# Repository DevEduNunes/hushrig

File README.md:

<div align="center">

# 🎸 HushRig

**Rig de guitarra open source para Windows — standalone e VST3.**
Toque direto no PC com baixa latência e sem chiado.

</div>

---

## Por que o HushRig?

Guitarra ligada direto no PC costuma dar dois problemas: **chiado** (captadores single coil, ganho alto, ruído da USB) e **delay** (drivers de áudio padrão do Windows com buffers grandes).
O HushRig ataca os dois: um **noise gate de latência zero** feito para guitarra e um caminho de áudio pensado para rodar com **ASIO**.

> ⚠️ Projeto em desenvolvimento ativo (v0.2). Gate, pedais, presets e amp sim NAM já funcionam; a interface com pedais visuais está no [roadmap](#-roadmap).

## ✨ Recursos

- **Medidor de latência**: mostra em ms a latência real reportada pelo driver (entrada, saída, buffer, CPU) com dicas para reduzir
- **Medidores de nível** de entrada e saída, com marcador do threshold e indicador de gate aberto/fechado
- **Pedais** de overdrive, EQ, chorus, delay e reverb, com ordem ajustável (arraste) e **presets** (de fábrica e seus)
- **Amp sim** com modelos `.nam` do [Neural Amp Modeler](https://www.neuralampmodeler.com/): 0 ms de latência adicionada, controles de ganho, graves/médios/agudos e volume, normalização de volume entre modelos e medidor de CPU
- **Noise gate** com threshold, hold e release — sem lookahead, ou seja, **zero latência** adicionada
- **Gravação em WAV** (24 bits, áudio já processado) com um clique, salva em Documentos\HushRig
- **Tema escuro** (preto e roxo) com knobs rotativos
- **Ganho de entrada e de saída** com transição suave (sem cliques)
- **Standalone e VST3** com o mesmo código
- **Entrada mono** espelhada nos dois canais (guitarra em estéreo no fone)
- **Janela redimensionável e botão de maximizar**: os cards se reorganizam em 1, 2 ou 3 colunas conforme o tamanho (monitor horizontal ou vertical) e podem ser arrastados para outra posição; a ordem fica salva
- **Atualização dentro do app**: ao abrir, procura novas versões no GitHub; se houver, aparece um ícone de download na barra de título e um clique baixa e instala
- **Instalador completo** que já instala o driver ASIO [FlexASIO](https://github.com/dechamps/FlexASIO)

## 🖼️ Screenshots

<table>
  <tr>
    <td align="center"><br><sub>Tela principal</sub></td>
  </tr>
</table>

> As imagens são geradas automaticamente pelo CI a cada build (`tools/Screenshots.cpp`). Os valores de latência e de nível nelas são **de exemplo**.

## 📦 Instalação

1. Baixe o `HushRig-Setup-x.y.z.exe` na página de [Releases](https://github.com/DevEduNunes/hushrig/releases).
2. Execute o instalador. Você escolhe os componentes:
   - **HushRig** (aplicativo)
   - **Plugin VST3** (instalado em `Common Files\VST3`)
   - **FlexASIO** (driver ASIO de baixa latência)
3. Abra o HushRig.

> O Windows pode mostrar o aviso do SmartScreen ("editor desconhecido"), porque o instalador ainda não é assinado digitalmente. Clique em **Mais informações → Executar assim mesmo**.

## 🎚️ Como usar

1. Conecte a interface de áudio e a guitarra. **Use fones** para evitar microfonia.
2. Em **Options** (canto do app), escolha o driver **ASIO → FlexASIO**, a entrada e a saída. Desmarque *Mute audio input*.
3. Reduza o **buffer** (comece com 256 amostras e vá descendo até começar a estalar) para diminuir a latência.
4. Ajuste o **Gate Threshold** até o chiado sumir quando você não está tocando. Se o gate cortar o fim das notas, aumente o **Release**.

| Parâmetro | O que faz |
|---|---|
| **Input Gain** | Ganho aplicado antes do gate |
| **Gate Threshold** | Nível abaixo do qual o gate fecha |
| **Gate Hold** | Tempo que o gate segura aberto depois que o sinal cai |
| **Gate Release** | Quão rápido o gate fecha |
| **Output Gain** | Volume de saída |
| **Gate bypass** | Desliga o gate |

### Pedais e presets

Ligue cada pedal no botão do canto do bloco. **Arraste o título** de um bloco para mudar a ordem da cadeia. O seletor **Presets** traz alguns de fábrica e guarda os seus (**Salvar**/**Excluir**), em `Documentos\HushRig\Presets`. Um preset guarda os pedais, a ordem e o modelo do amp; ganhos e gate ficam como você deixou.

### Amp sim (modelos NAM)

1. No bloco **AMP (NAM)**, clique em **Carregar modelo...** e escolha um arquivo `.nam` (ou um `.wav` de IR). Há muitos modelos gratuitos feitos pela comunidade do [Neural Amp Modeler](https://www.neuralampmodeler.com/).
2. O bloco mostra quanto do tempo do buffer o modelo usa (**CPU**). Se ficar alto (laranja/vermelho) ou o som estalar, troque por um modelo mais leve ou aumente o buffer.
3. No card **AMP · GANHO E TOM** ajuste:

| Controle | O que faz |
|---|---|
| **Input** | Ganho antes do modelo (empurra o amp para mais ou menos distorção) |
| **Bass / Mid / Treble** | Tom, aplicado depois do modelo (±12 dB) |
| **Output** | Volume de saída do amp |
| **Normalizar volume** | Iguala o volume entre modelos usando o loudness gravado no `.nam` |

O amp **não adiciona latência**. Se o modelo foi treinado em uma taxa diferente da do dispositivo (por exemplo 48 kHz no modelo e 44,1 kHz no driver), o bloco avisa, porque o timbre muda: prefira rodar a 48 kHz.

### Dicas contra o chiado

O software ajuda, mas confira também a origem:
- Ganho do preamp da interface alto demais
- Captadores single coil (chegar perto do monitor aumenta o zumbido)
- Notebook ligado na fonte (teste na bateria) e outra porta USB
- Cabo da guitarra

## 🔄 Atualizações

No app standalone, toda vez que você abre o HushRig ele procura uma versão nova no GitHub. Se houver, aparece um ícone de download com o número da versão na barra de título: clique nele e o app baixa o instalador da release, confere o SHA-256 e reinicia já atualizado.

## 🗺️ Roadmap

- [x] Esqueleto JUCE (Standalone + VST3) e CI no GitHub Actions
- [x] Noise gate (threshold, hold, release) com testes
- [x] Instalador com FlexASIO e atualização dentro do app
- [x] Medidor de latência e medidores de nível
- [x] Pedais: overdrive, delay, reverb, chorus e EQ
- [x] Cadeia de pedais reordenável (arraste o título) e presets
- [x] Gravação em WAV
- [x] Amp sim com modelos [Neural Amp Modeler](https://www.neuralampmodeler.com/) (carregue um `.nam`; latência adicional zero)
- [ ] Interface própria com pedais visuais
- [~] [HushRig em hardware](docs/hardware/README.md): pedal com ESP32 (~US$ 14), controlado pelo celular por Bluetooth (esquemático, PCB e firmware prontos; falta montar e validar em placa real)

## 🛠️ Compilando

O build oficial roda no GitHub Actions (`.github/workflows/build.yml`). Para compilar localmente você precisa do Visual Studio 2022 (carga de trabalho C++) e do CMake:

```bash
cmake -B build -DCMAKE_BUILD_TYPE=Release
cmake --build build --config Release
ctest --test-dir build -C Release --output-on-failure
```

Os binários ficam em `build/HushRig_artefacts/Release/`.

```
src/dsp/        # DSP sem dependência do JUCE (testável; também usado pelo firmware)
firmware/       # pedal em hardware (ESP32-S3), ver docs/hardware/
src/update/     # verificação de versão, SHA-256 e atualizador
src/            # processador e editor do plugin
tests/          # testes (Catch2)
tools/          # gerador de screenshots do README e hushrig_ampbench (mede o custo de um modelo .nam)
installer/      # script do instalador (Inno Setup)
```

## 🤝 Contribuindo

Issues e pull requests são bem-vindos. Para lançar uma versão, crie uma tag `vX.Y.Z`: o CI compila e publica a release com o instalador.

### Medindo um modelo NAM

O `hushrig_ampbench` (compilado junto com o projeto) mostra quanto do tempo do buffer um modelo usa, em buffers de 64 a 512 amostras:

```bash
build/Release/hushrig_ampbench.exe meu-modelo.nam 48000
```

Abaixo de ~50% (p99) é seguro; acima disso prefira um modelo mais leve ou um buffer maior.

## 📄 Licença

[AGPL-3.0](LICENSE), compatível com a licença do [JUCE](https://juce.com).

O amp sim usa o [NeuralAmpModelerCore](https://github.com/sdatkinson/NeuralAmpModelerCore) (MIT), que inclui o [Eigen](https://eigen.tuxfamily.org) (MPL-2.0) e o [nlohmann/json](https://github.com/nlohmann/json) (MIT). Os modelos de teste em `tests/data/` vêm do repositório do NAM Core.

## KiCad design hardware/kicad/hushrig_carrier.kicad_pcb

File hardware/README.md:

# HushRig Carrier v1 — esquemático e PCB (KiCad 7)

Placa carrier para o pedal HushRig: recebe um **ESP32-DevKitC de 38 pinos** em soquetes, tem o **buffer de entrada** para a guitarra, a alimentação analógica filtrada e conectores para jacks, footswitch, LED, potenciômetro e bateria. Os módulos **PCM1808** (ADC) e **PCM5102A** (DAC) ligam por cabinhos (cada fabricante usa um pinout diferente). Detalhes, cabeamento e avisos: [docs/hardware/README.md](../docs/hardware/README.md).

```
kicad/      projeto do KiCad (hushrig_carrier.kicad_pro), esquemático (.kicad_sch + PDF) e PCB (.kicad_pcb)
gerbers/    gerbers + furação + zip pronto para a fábrica
bom.csv     lista de materiais agrupada
tools/      geradores e verificações (tudo sai de tools/netlist.py)
```

## Regenerar e conferir

```bash
sudo apt install kicad                  # KiCad 7 (kicad-cli e pcbnew em Python)
pip install kiutils shapely numpy cairosvg
cd hardware/tools
python3 gen_sch.py && python3 verify_sch.py     # esquemático; netlist do KiCad == netlist.py
python3 gen_pcb.py && python3 verify_pcb.py     # posiciona, roteia, preenche o GND; DRC e conectividade
./export.sh                                     # gerbers, furação, zip e bom.csv
```

`netlist.py` é a fonte única: peças, ligações e footprints. Para mover uma peça, edite `PLACE` em `gen_pcb.py`; para mudar uma ligação, edite `netlist.py` e rode tudo de novo.

## O que foi (e não foi) verificado

- ✅ Netlist do esquemático idêntica à de `netlist.py` (28 redes).
- ✅ DRC próprio (`verify_pcb.py`): folga cobre-cobre ≥ 0,2 mm, trilha ≥ 0,2 mm, anel de via ≥ 0,15 mm, folga entre furos ≥ 0,25 mm, borda ≥ 0,3 mm, todas as redes conectadas (inclui o preenchimento do GND).
- ⚠️ **ERC e DRC do KiCad não foram rodados** (o KiCad 7 só os oferece na interface gráfica; na linha de comando só no 8). Rode os dois antes de fabricar.
- ⚠️ **Nenhuma placa foi montada.** O pinout dos 38 pinos do DevKit segue o DevKitC/NodeMCU-32S; confira na sua placa.

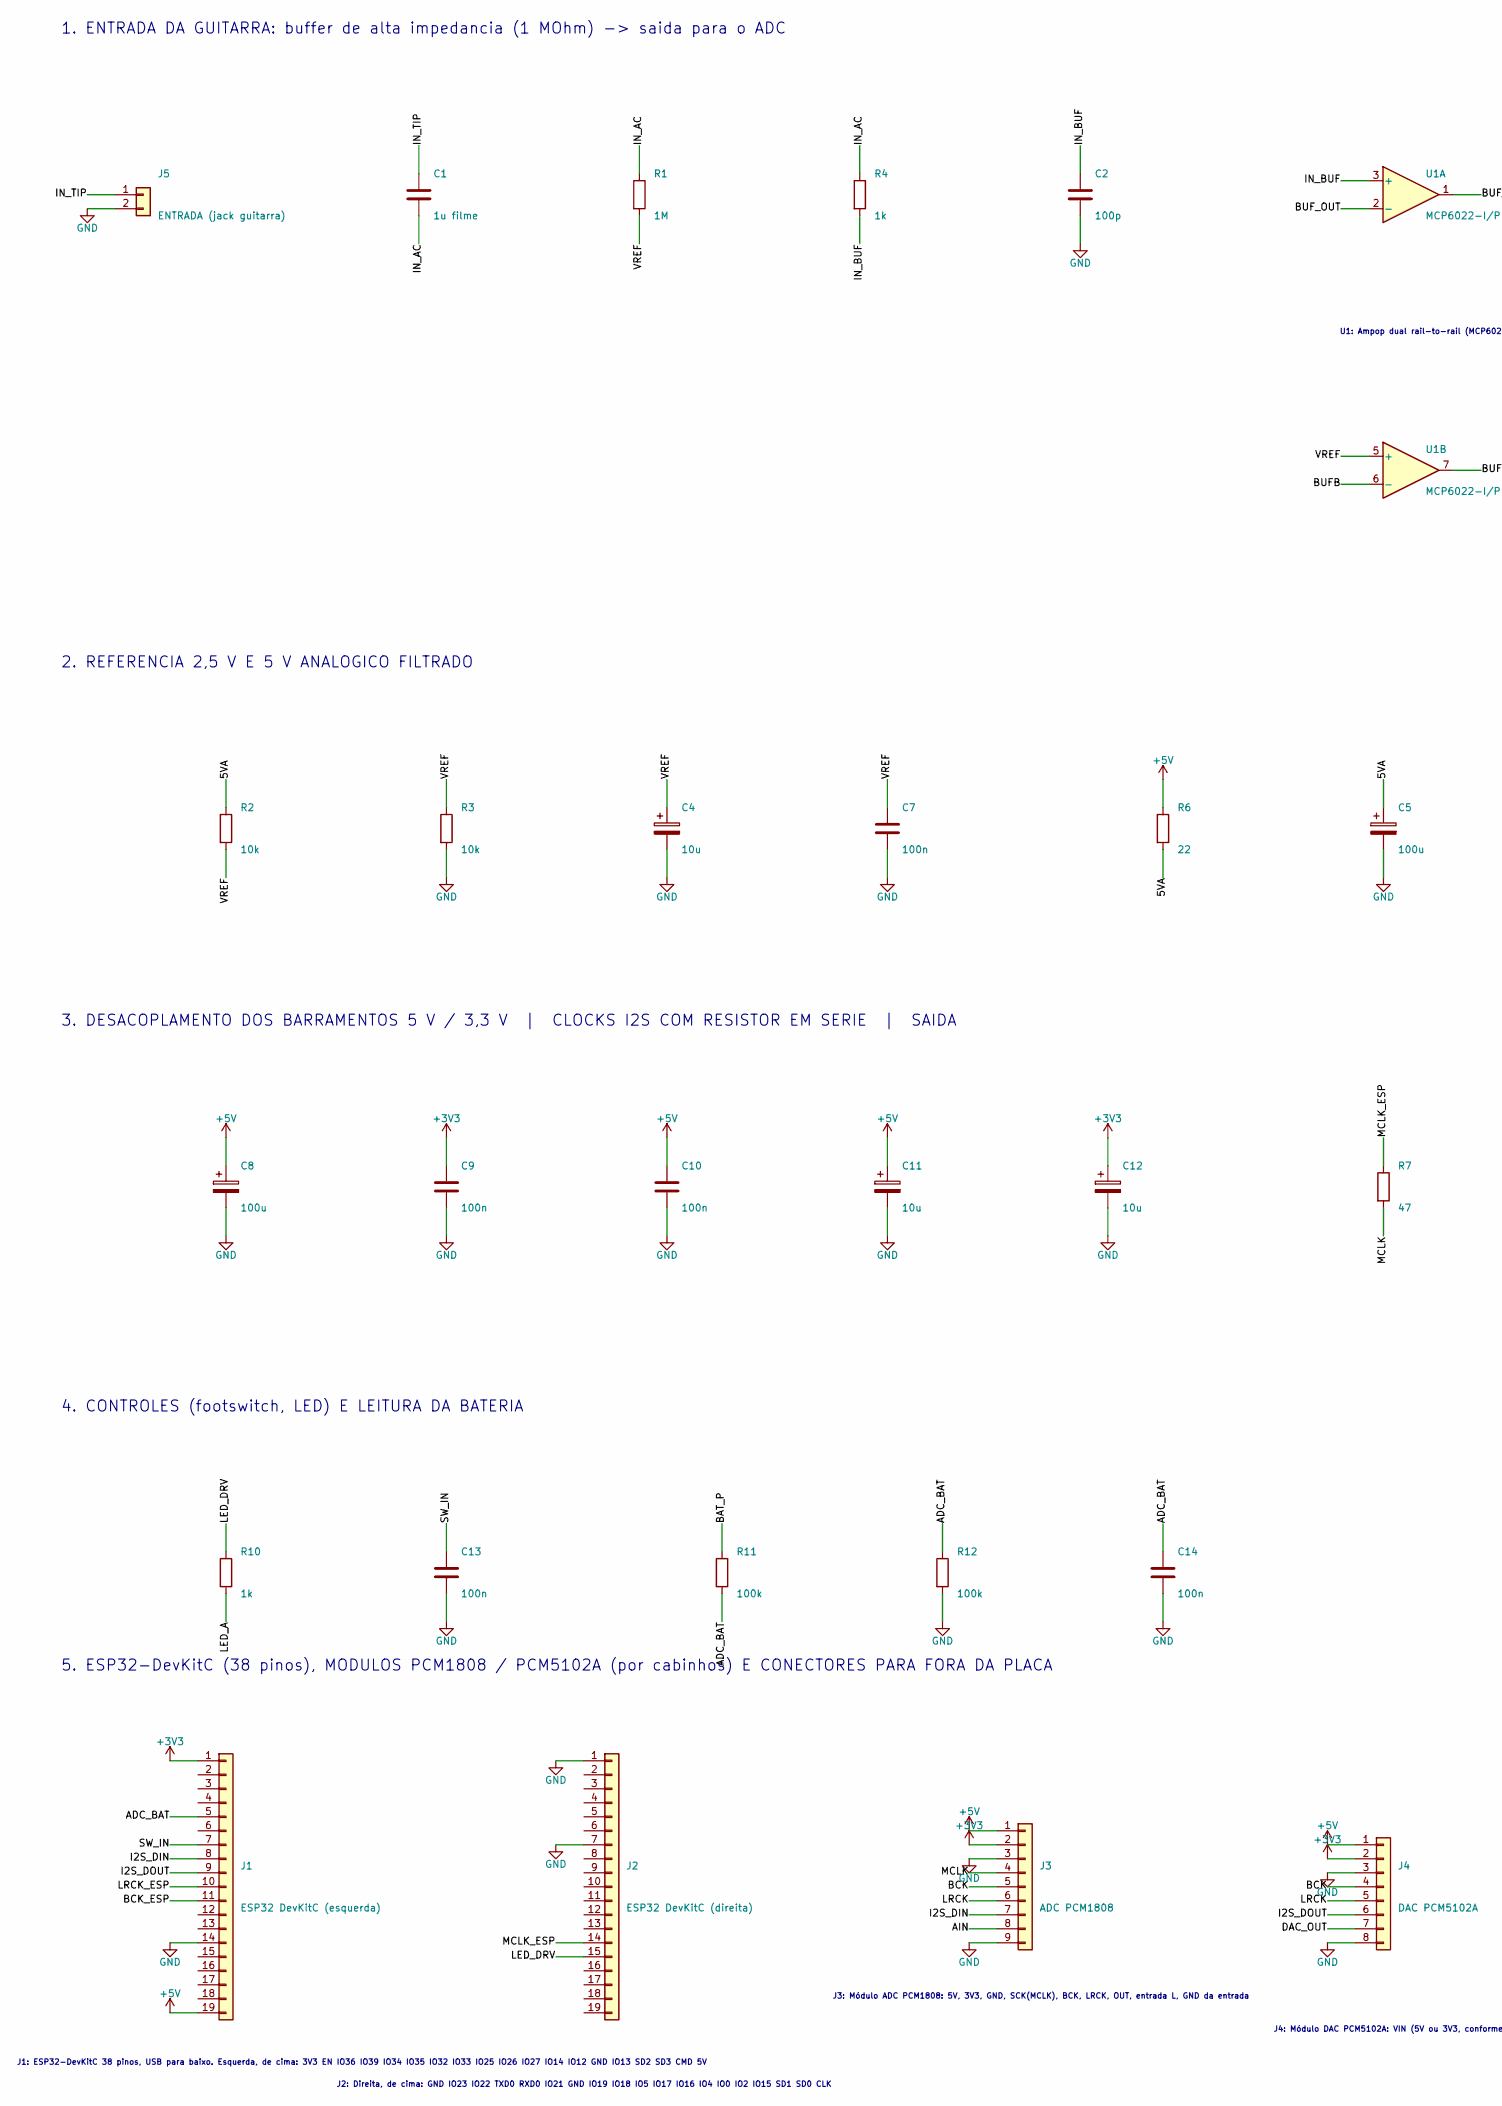
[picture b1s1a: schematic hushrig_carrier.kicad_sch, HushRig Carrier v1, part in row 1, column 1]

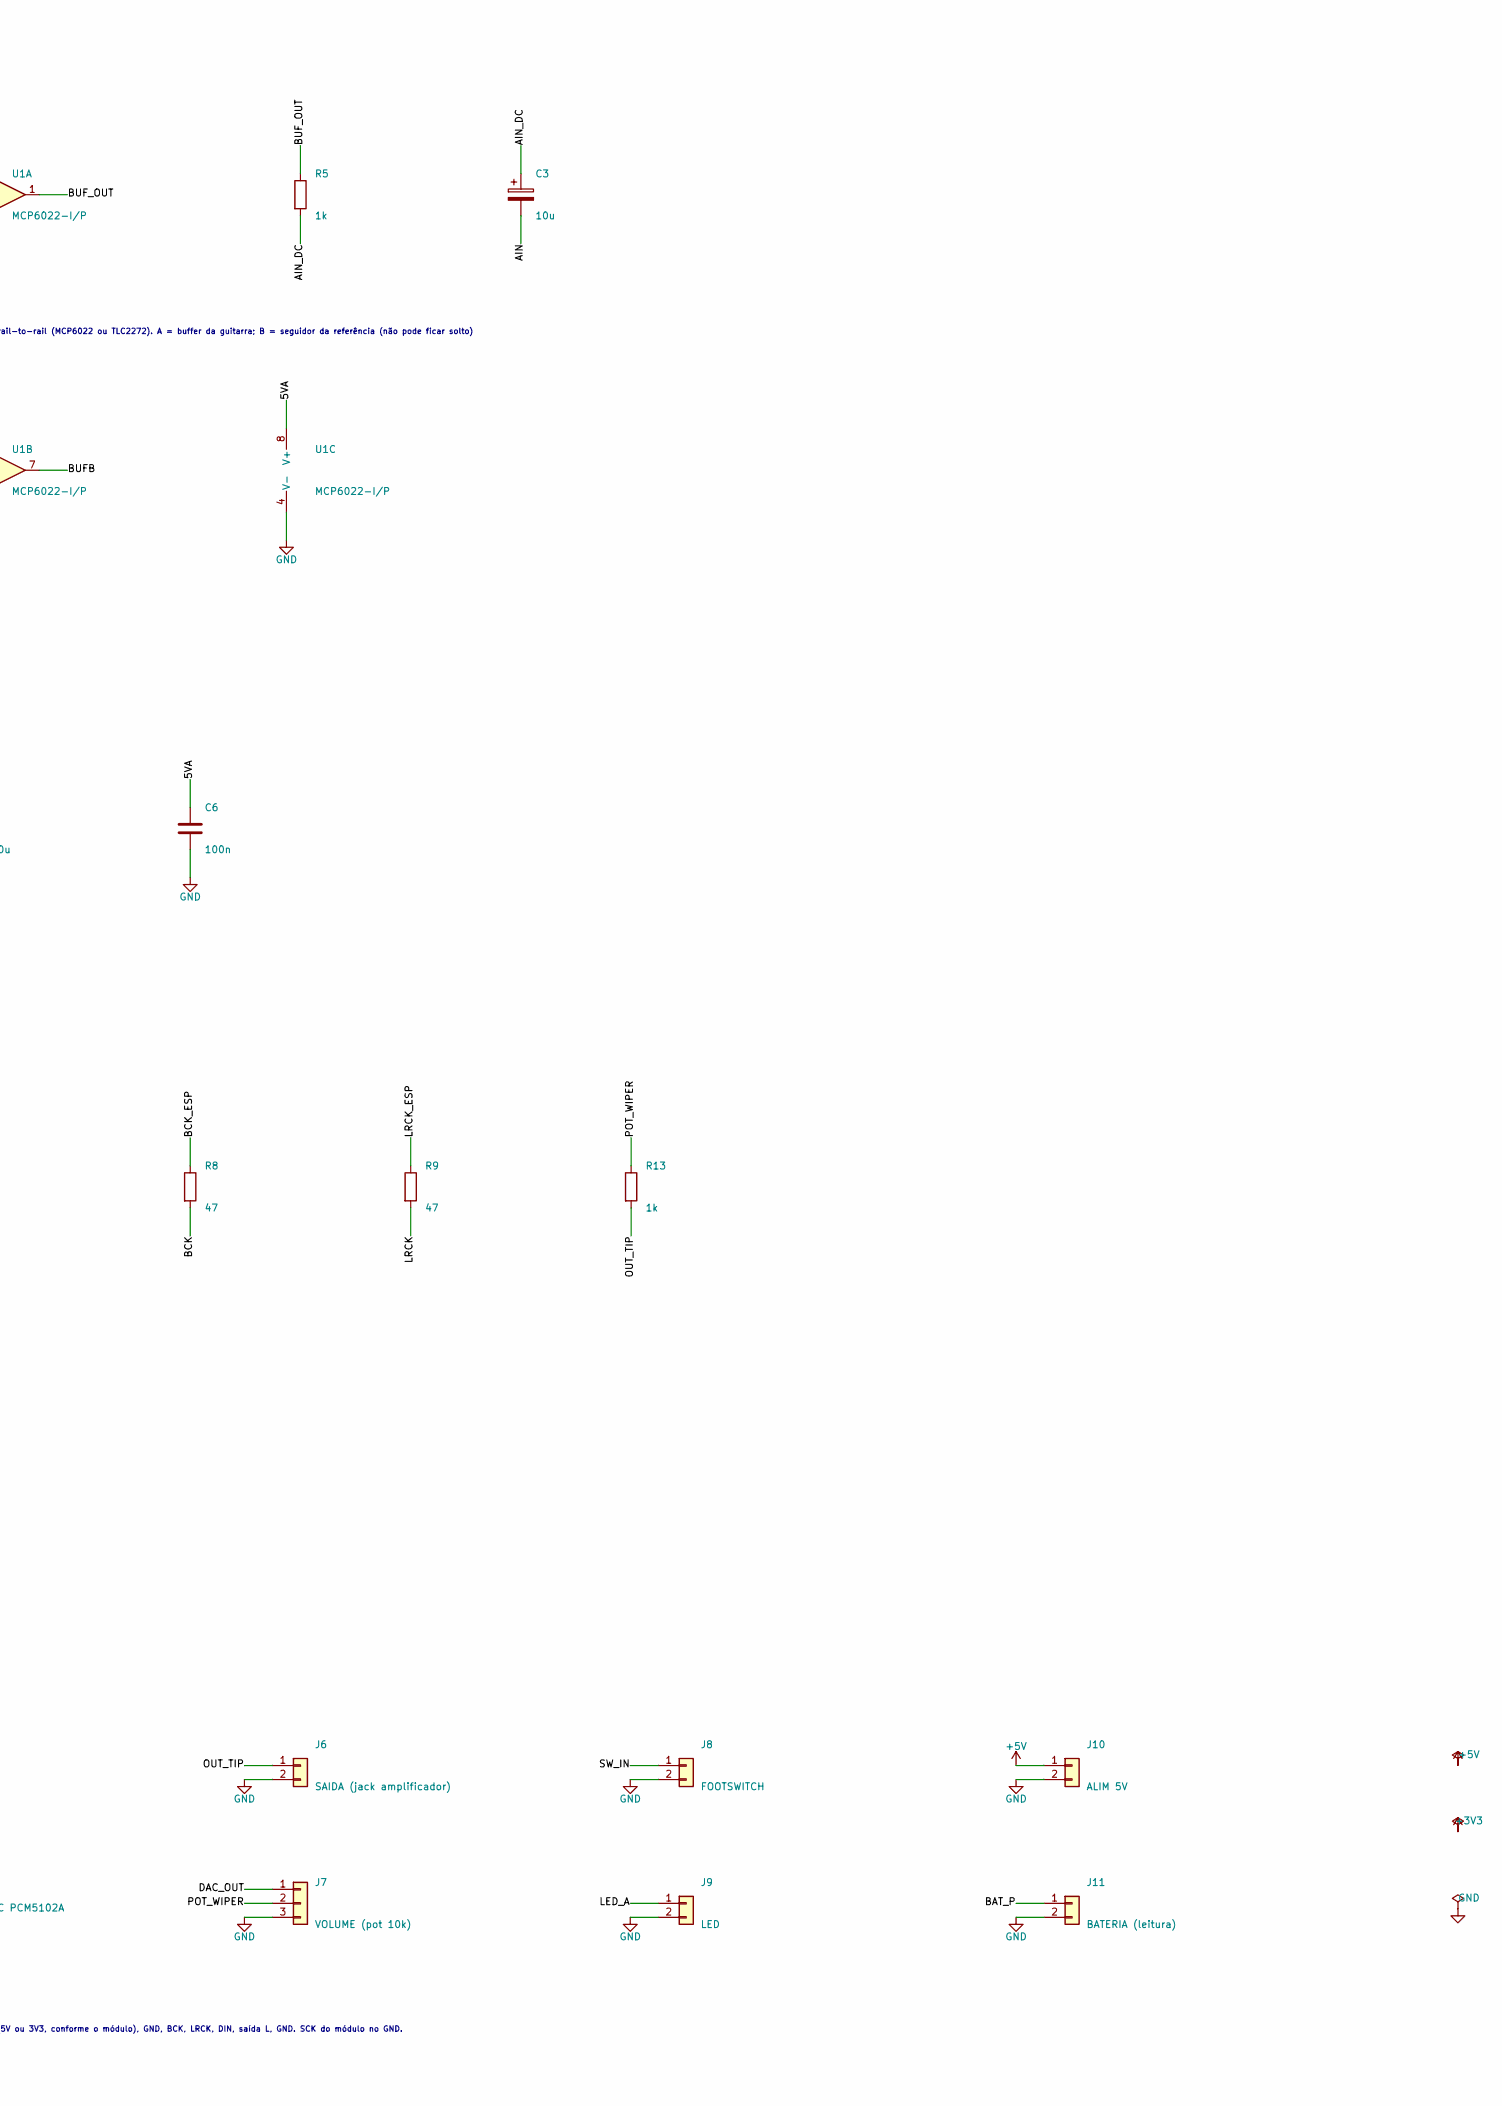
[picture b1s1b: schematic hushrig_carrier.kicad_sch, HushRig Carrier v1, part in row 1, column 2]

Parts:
C1: 1u filme; C_Rect_L7.2mm_W3.0mm_P5.00mm_FKS2_FKP2_MKS2_MKP2
C2: 100p; C_Disc_D5.0mm_W2.5mm_P5.00mm
C3, C4, C11, C12: 10u; CP_Radial_D5.0mm_P2.00mm
C5, C8: 100u; CP_Radial_D6.3mm_P2.50mm
C6, C7, C9, C10, C13, C14: 100n; C_Disc_D5.0mm_W2.5mm_P5.00mm
J1: ESP32 DevKitC (esquerda); PinSocket_1x19_P2.54mm_Vertical
J2: ESP32 DevKitC (direita); PinSocket_1x19_P2.54mm_Vertical
J3: ADC PCM1808; PinHeader_1x09_P2.54mm_Vertical
J4: DAC PCM5102A; PinHeader_1x08_P2.54mm_Vertical
J5: ENTRADA (jack guitarra); PinHeader_1x02_P2.54mm_Vertical
J6: SAIDA (jack amplificador); PinHeader_1x02_P2.54mm_Vertical
J7: VOLUME (pot 10k); PinHeader_1x03_P2.54mm_Vertical
J8: FOOTSWITCH; PinHeader_1x02_P2.54mm_Vertical
J9: LED; PinHeader_1x02_P2.54mm_Vertical
J10: ALIM 5V; PinHeader_1x02_P2.54mm_Vertical
J11: BATERIA (leitura); PinHeader_1x02_P2.54mm_Vertical
R1: 1M; R_Axial_DIN0207_L6.3mm_D2.5mm_P7.62mm_Horizontal
R2, R3: 10k; R_Axial_DIN0207_L6.3mm_D2.5mm_P7.62mm_Horizontal
R4, R5, R10, R13: 1k; R_Axial_DIN0207_L6.3mm_D2.5mm_P7.62mm_Horizontal
R6: 22; R_Axial_DIN0207_L6.3mm_D2.5mm_P7.62mm_Horizontal
R7, R8, R9: 47; R_Axial_DIN0207_L6.3mm_D2.5mm_P7.62mm_Horizontal
R11, R12: 100k; R_Axial_DIN0207_L6.3mm_D2.5mm_P7.62mm_Horizontal
U1: MCP6022-I/P; DIP-8_W7.62mm_Socket

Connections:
5VA: C5.1, C6.1, R2.1, R6.2, U1.8 (V+)
+3V3: C9.1, C12.1, J1.1, J3.2, J4.2
+5V: C8.1, C10.1, C11.1, J1.19, J3.1, J4.1, J10.1, R6.1
ADC_BAT: C14.1, J1.5, R11.2, R12.1
AIN: C3.2, J3.8
AIN_DC: C3.1, R5.2
BAT_P: J11.1, R11.1
BCK: J3.5, J4.4, R8.2
BCK_ESP: J1.11, R8.1
BUFB: U1.6 (-), U1.7
BUF_OUT: R5.1, U1.1, U1.2 (-)
DAC_OUT: J4.7, J7.1
GND: C2.2, C4.2, C5.2, C6.2, C7.2, C8.2, C9.2, C10.2, C11.2, C12.2, C13.2, C14.2, J1.14, J2.1, J2.7, J3.3, J3.9, J4.3, J4.8, J5.2, J6.2, J7.3, J8.2, J9.2, J10.2, J11.2, R3.2, R12.2, U1.4 (V-)
I2S_DIN: J1.8, J3.7
I2S_DOUT: J1.9, J4.6
IN_AC: C1.2, R1.1, R4.1
IN_BUF: C2.1, R4.2, U1.3 (+)
IN_TIP: C1.1, J5.1
LED_A: J9.1, R10.2
LED_DRV: J2.15, R10.1
LRCK: J3.6, J4.5, R9.2
LRCK_ESP: J1.10, R9.1
MCLK: J3.4, R7.2
MCLK_ESP: J2.14, R7.1
OUT_TIP: J6.1, R13.2
POT_WIPER: J7.2, R13.1
SW_IN: C13.1, J1.7, J8.1
VREF: C4.1, C7.1, R1.2, R2.2, R3.1, U1.5 (+)

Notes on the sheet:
1. ENTRADA DA GUITARRA: buffer de alta impedancia (1 MOhm) -> saida para o ADC
2. REFERENCIA 2,5 V E 5 V ANALOGICO FILTRADO
3. DESACOPLAMENTO DOS BARRAMENTOS 5 V / 3,3 V | CLOCKS I2S COM RESISTOR EM SERIE | SAIDA
4. CONTROLES (footswitch, LED) E LEITURA DA BATERIA
5. ESP32-DevKitC (38 pinos), MODULOS PCM1808 / PCM5102A (por cabinhos) E CONECTORES PARA FORA DA PLACA
U1: Ampop dual rail-to-rail (MCP6022 ou TLC2272). A = buffer da guitarra; B = seguidor da referência (não pode ficar solto)
J1: ESP32-DevKitC 38 pinos, USB para baixo. Esquerda, de cima: 3V3 EN IO36 IO39 IO34 IO35 IO32 IO33 IO25 IO26 IO27 IO14 IO12 GND IO13 SD2 SD3 CMD 5V
J2: Direita, de cima: GND IO23 IO22 TXD0 RXD0 IO21 GND IO19 IO18 IO5 IO17 IO16 IO4 IO0 IO2 IO15 SD1 SD0 CLK
J3: Módulo ADC PCM1808: 5V, 3V3, GND, SCK(MCLK), BCK, LRCK, OUT, entrada L, GND da entrada
J4: Módulo DAC PCM5102A: VIN (5V ou 3V3, conforme o módulo), GND, BCK, LRCK, DIN, saída L, GND. SCK do módulo no GND.

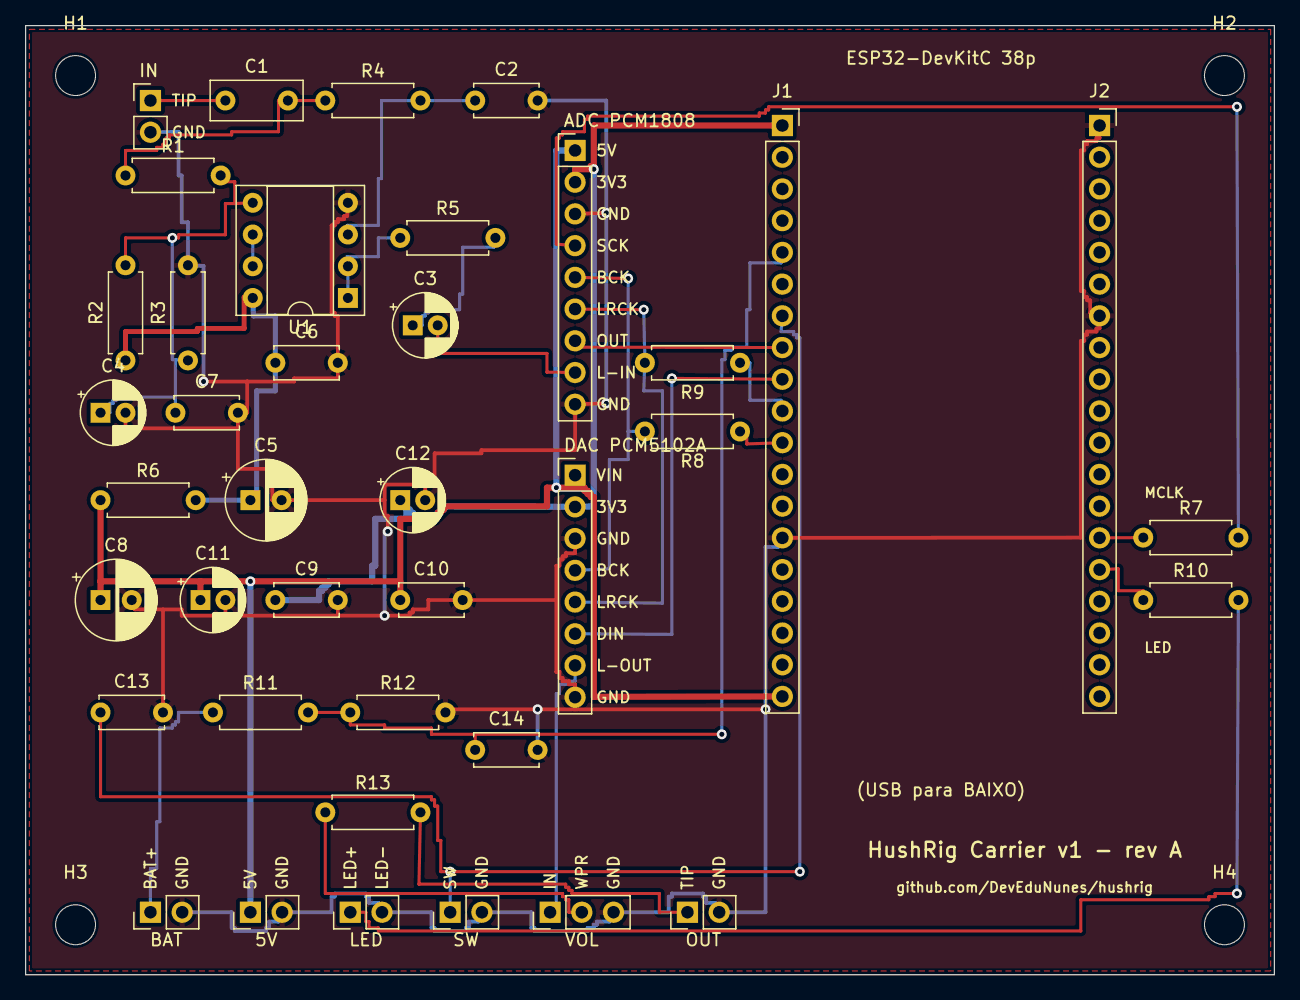
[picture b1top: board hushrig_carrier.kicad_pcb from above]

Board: 2 copper layers, 100.0 x 76.0 mm, 43 parts (0 on the bottom side), 28 nets.

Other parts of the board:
H1, H2, H3, H4: M3; MountingHole_3.2mm_M3

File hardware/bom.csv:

Qtd,Referências,Valor,Footprint,Observação
2,R11 R12,100k,R_Axial_DIN0207_L6.3mm_D2.5mm_P7.62mm_Horizontal,"Resistor 1/4 W 5% (ou 1%), furo passante"
6,C6 C7 C9 C10 C13 C14,100n,C_Disc_D5.0mm_W2.5mm_P5.00mm,"Capacitor cerâmico 100 nF, passo 5 mm"
1,C2,100p,C_Disc_D5.0mm_W2.5mm_P5.00mm,"Capacitor cerâmico 100 pF, passo 5 mm"
2,C5 C8,100u,CP_Radial_D6.3mm_P2.50mm,Capacitor eletrolítico radial (≥ 16 V)
2,R2 R3,10k,R_Axial_DIN0207_L6.3mm_D2.5mm_P7.62mm_Horizontal,"Resistor 1/4 W 5% (ou 1%), furo passante"
4,C3 C4 C11 C12,10u,CP_Radial_D5.0mm_P2.00mm,Capacitor eletrolítico radial (≥ 16 V)
1,R1,1M,R_Axial_DIN0207_L6.3mm_D2.5mm_P7.62mm_Horizontal,"Resistor 1/4 W 5% (ou 1%), furo passante"
4,R4 R5 R10 R13,1k,R_Axial_DIN0207_L6.3mm_D2.5mm_P7.62mm_Horizontal,"Resistor 1/4 W 5% (ou 1%), furo passante"
1,C1,1u filme,C_Rect_L7.2mm_W3.0mm_P5.00mm_FKS2_FKP2_MKS2_MKP2,"Capacitor de filme 1 uF (poliéster/MKT), passo 5 mm"
1,R6,22,R_Axial_DIN0207_L6.3mm_D2.5mm_P7.62mm_Horizontal,"Resistor 1/4 W 5% (ou 1%), furo passante"
3,R7 R8 R9,47,R_Axial_DIN0207_L6.3mm_D2.5mm_P7.62mm_Horizontal,"Resistor 1/4 W 5% (ou 1%), furo passante"
1,J3,ADC PCM1808,PinHeader_1x09_P2.54mm_Vertical,"Barra de pinos 2,54 mm macho"
1,J10,ALIM 5V,PinHeader_1x02_P2.54mm_Vertical,"Barra de pinos 2,54 mm macho"
1,J11,BATERIA (leitura),PinHeader_1x02_P2.54mm_Vertical,"Barra de pinos 2,54 mm macho"
1,J4,DAC PCM5102A,PinHeader_1x08_P2.54mm_Vertical,"Barra de pinos 2,54 mm macho"
1,J5,ENTRADA (jack guitarra),PinHeader_1x02_P2.54mm_Vertical,"Barra de pinos 2,54 mm macho"
1,J2,ESP32 DevKitC (direita),PinSocket_1x19_P2.54mm_Vertical,"Barra de pinos 2,54 mm fêmea (soquete do DevKit)"
1,J1,ESP32 DevKitC (esquerda),PinSocket_1x19_P2.54mm_Vertical,"Barra de pinos 2,54 mm fêmea (soquete do DevKit)"
1,J8,FOOTSWITCH,PinHeader_1x02_P2.54mm_Vertical,"Barra de pinos 2,54 mm macho"
1,J9,LED,PinHeader_1x02_P2.54mm_Vertical,"Barra de pinos 2,54 mm macho"
1,U1,MCP6022-I/P,DIP-8_W7.62mm_Socket,MCP6022-I/P (DIP-8) ou TLC2272; use soquete DIP-8
1,J6,SAIDA (jack amplificador),PinHeader_1x02_P2.54mm_Vertical,"Barra de pinos 2,54 mm macho"
1,J7,VOLUME (pot 10k),PinHeader_1x03_P2.54mm_Vertical,"Barra de pinos 2,54 mm macho"

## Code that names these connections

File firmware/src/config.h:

#pragma once

#include "driver/gpio.h"
#include "hal/adc_types.h"
#include "sdkconfig.h"

// Ligações e ajustes da placa. Veja docs/hardware/README.md para o esquema completo.

// Transportes de controle (platformio.ini define por ambiente). O ESP32 barato usa só BLE.
#ifndef HUSHRIG_BLE
#define HUSHRIG_BLE 1
#endif
#ifndef HUSHRIG_WIFI
#define HUSHRIG_WIFI 0
#endif

namespace cfg
{
// --- Áudio (I2S full-duplex, o ESP32 é o mestre do clock) ---------------------
constexpr int kSampleRate  = 48000;
constexpr int kBlockFrames = 32; // 32 = ~0,7 ms por bloco. Se estalar, suba para 64.

#if CONFIG_IDF_TARGET_ESP32S3
// ESP32-S3
constexpr gpio_num_t kI2sMclk = GPIO_NUM_4; // -> SCK/SCKI do PCM1808 (o PCM5102A usa PLL interno)
constexpr gpio_num_t kI2sBclk = GPIO_NUM_5; // -> BCK de PCM1808 e PCM5102A
constexpr gpio_num_t kI2sWs   = GPIO_NUM_6; // -> LRCK de PCM1808 e PCM5102A
constexpr gpio_num_t kI2sDout = GPIO_NUM_7; // -> DIN do PCM5102A
constexpr gpio_num_t kI2sDin  = GPIO_NUM_8; // <- OUT do PCM1808
constexpr gpio_num_t kFootswitch = GPIO_NUM_9;  // botão para GND (pull-up interno)
constexpr gpio_num_t kLed        = GPIO_NUM_10; // LED (com resistor 1k) aceso = efeito ligado
constexpr adc_channel_t kBatteryChannel = ADC_CHANNEL_0; // GPIO1
#else
// ESP32 clássico, DevKitC de 38 pinos (o de 30 pinos NÃO expõe o GPIO0). No ESP32 o MCLK do I2S só sai nos GPIO0, 1 ou 3.
constexpr gpio_num_t kI2sMclk = GPIO_NUM_0;
constexpr gpio_num_t kI2sBclk = GPIO_NUM_27;
constexpr gpio_num_t kI2sWs   = GPIO_NUM_26;
constexpr gpio_num_t kI2sDout = GPIO_NUM_25;
constexpr gpio_num_t kI2sDin  = GPIO_NUM_33;
constexpr gpio_num_t kFootswitch = GPIO_NUM_32;
constexpr gpio_num_t kLed        = GPIO_NUM_2; // LED azul da própria placa na maioria dos DevKits
constexpr adc_channel_t kBatteryChannel = ADC_CHANNEL_6; // GPIO34 (só entrada)
#endif

// Divisor 100k/100k do + da bateria até o pino acima. Sem bateria (power bank), a leitura fica ~0 e a UI mostra 0%.
constexpr float kBatteryDivider = 2.0f;

// --- BLE ----------------------------------------------------------------------
constexpr const char* kBleName = "HushRig";

// --- WiFi (só se HUSHRIG_WIFI=1): ponto de acesso do próprio pedal ---------------
// TROQUE a senha antes de usar em público. Mínimo de 8 caracteres.
constexpr const char* kApSsid     = "HushRig";
constexpr const char* kApPassword = "hushrig123";
constexpr int kApChannel = 6;
constexpr int kApMaxClients = 2;
} // namespace cfg

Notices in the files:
README.md:
https://img.shields.io/badge/licen%C3%A7a-AGPL--3.0-green
hardware/kicad/hushrig_carrier.kicad_sch:
Licenca AGPL-3.0. Gerado por hardware/tools/gen_sch.py
